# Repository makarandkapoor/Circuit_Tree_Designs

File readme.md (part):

## Synopsis

The folder contains embedded hardware designs mined/created by circuit tree hardware compiler. The designs are auto generated by scripts which generate each of the 900+ processors/microcontrollers parts with the various embedded component library list of circuit tree. Script help in generation of various design files and autogenerate componnent placements for the various dxf files present on circuit tree server. For additional details about the hardware compiler visit [Circuit Tree](https://circuit-tree.com). 

## Folder contents

Each folder contains design files generated on the circuit tree application server. It contains eagle, altium and orcad schematic files , bill of material, board layout snapshots from various dxf file to display auto generated component placement. 

Additional folder Development boards contains projects which have been fabricated and assembled. [Small Drone board](https://github.com/makarandkapoor/Circuit_Tree_Designs/tree/master/Development_boards/Small_drone_board) is a example board created with circuit tree hardware compiler. 

## Motivation

The purpose of generating design is to allow individuals to use vast generated design content without restriction and provide any feedback/improvement areas. 

## Fun Fact

Fun Fact: Each Design took 4-6 minutes to generate through scripts. We are talking about design generation, export of various EDA cad files, random board component placements of 6 boards for 900 + controllers that totals 3600 minutes(60 hrs)(Two and half day). 
It's time to look for a entry in some record book :) 

## Featured Hardware designs of the controllers
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
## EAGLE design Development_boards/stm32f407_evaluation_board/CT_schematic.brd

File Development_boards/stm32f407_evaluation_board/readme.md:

Contains the reference design files from the blog post

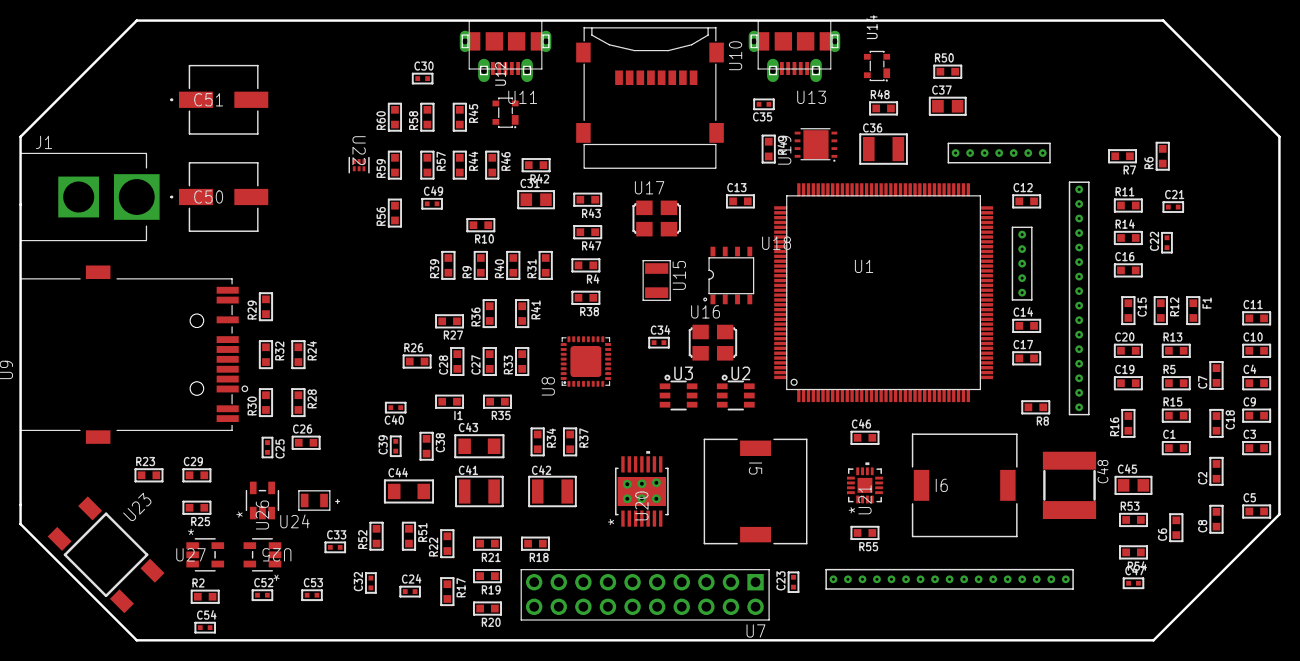
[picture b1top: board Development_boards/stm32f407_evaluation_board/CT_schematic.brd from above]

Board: 2 copper layers, 130.0 x 64.0 mm, 145 parts (0 on the bottom side), 118 nets, no tracks yet.

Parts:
C1, C20, C26, C27, C29, C38, C46: 1e-06; C0603
C2, C3, C4, C5, C6, C7, C8, C9, C10, C11, C12, C13, C17, C18: 1e-07; C0603
C14: 4.7e-06; C0603
C15, C16: 2.2e-06; C0603
C19: 1e-08; C0603
C21, C22: 1e-11; C0402
C23, C24, C30, C40, C47, C49: 1e-07; C0402
C25: 2.2e-08; C0402
C28: 4.7e-10; C0603
C31, C37, C45: 1e-05; C0805
C32, C33, C34, C35, C52, C53, C54: 1e-08; C0402
C36: 1e-05; C1210
C39: 3.3e-09; C0402
C41, C42: 2.2e-05; C1210
C43, C44: 1e-05; C1206
C48: 6.8e-05; 2220
C50, C51: 0.0001; EXV-9H
F1: 240.0; L0603
I1: 97.0; R0603
I5: 5.2e-06; DR1040
I6: 7e-06; DR1040
J1: PJ-037B; PJ-037B_PACKAGE
R2, R50: 1000.0; R0603
R4, R5: 4700.0; R0603
R6, R7, R8, R9, R10: 2200.0; R0603
R11, R12: 47000.0; R0603
R13, R14, R15, R16, R17, R18, R19, R20, R21, R22, R31, R33, R34, R35, R36, R37, R38, R39, R40, R41, R56, R57: 10000.0; R0603
R23, R24: 0.1; R0603
R25, R26, R49: 200.0; R0603
R27: 12100.0; R0603
R28, R29, R30, R32: 49.9; R0603
R42, R43, R44, R45, R46, R47, R48: 100000.0; R0603
R51: 71007.101651032; R0603
R52: 22000.0; R0603
R53: 20000.0; R0603
R54: 150000.0; R0603
R55: 300000.0; R0603
R58: 9100.0; R0603
R59: 680000.0; R0603
R60: 120000.0; R0603
U1: STM32F407ZET6; LQFP144
U2, U3: MAX4995AAUT+T; SOT-23-6
U4: dummy_connector_j2; DUMMY_PACKAGE_286
U5: dummy_connector_j4; DUMMY_PACKAGE_290
U6: dummy_connector_j5; DUMMY_PACKAGE_292
U7: TST-110-05-T-D-RA
U8: LAN8710AI-EZK; QFN-32
U9: 7498011122R
U10: 0472192001; MOLEX_47219-2001
U11, U13: 47590-0001; MICRO_USB_AB
U12, U14: prtr5v0u2ax; SOT143B
U15: ABS07-32.768KHZ-7-T
U16: ASFL1-25MHZ-NCS; ASFL1
U17: ASFL1-50MHZ-NCS; ASFL1
U18: idt74fct38072; IDT74FCT38072
U19: LP3878SDX-ADJ/NOPB; WSON-8
U20: tps54325PWP; HTSSOP14
U21: LTC3601EUD#PBF; QFN-16_EP
U22: TPS3895ADRYR; SON-6
U23: 4-1437565-2; SW_4-1437565-2
U24: Q65110A2395; LGM67K-G1J2-24-Z
U25, U26, U27: nc7sz125m5x; NC7SZ125M5X
U28: Dummy; DUMMY_PACKAGE_307

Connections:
CLK_CRYSTAL_U1_8: C21.1, U1.8, U15.1
CLK_CRYSTAL_U1_9: C22.1, U1.9, U15.2
CLK_U1_23: U1.23, U16.3
CLK_U1_35: U1.35, U18.7
CLK_U8_5: U8.5, U18.6
CLK_U18_3: U17.3, U18.3
GND: C1.2, C2.2, C3.2, C4.2, C5.2, C6.2, C7.2, C8.2, C9.2, C10.2, C11.2, C12.2, C13.2, C14.2, C15.2, C16.2, C17.2, C18.2, C19.2, C20.2, C21.2, C22.2, C23.2, C24.2, C25.2, C26.2, C27.2, C28.2, C29.2, C30.2, C31.2, C32.2, C33.2, C34.2, C35.2, C36.2, C37.2, C38.2, C39.2, C41.2, C42.2, C43.2, C44.2, C45.2, C46.2, C48.1, C49.2, C50.2, C51.2, C52.2, C53.2, C54.2, J1.2, R2.2, R11.2, R12.2, R14.2, R16.2, R22.2, R23.2, R24.2, R25.2, R27.2, R33.2, R41.2, R50.2, R52.2, R53.2, R55.2, R58.2, R60.2, U1.16, U1.31, U1.38, U1.51, U1.61, U1.83, U1.94, U1.107, U1.120, U1.130, U2.2, U3.2, U4.1, U4.6, U4.11, U5.1, U6.1, U6.6, U7.4, U7.6, U7.8, U7.10, U7.12, U7.14, U7.16, U7.18, U7.20, U8.24, U8.25, U8.EXP, U10.6, U10.G1, U10.G2, U10.G3, U10.G4, U11.5, U12.1, U13.5, U14.1, U16.2, U17.2, U18.4, U18.5, U18.8, U19.3, U19.PAD, U20.5, U21.1, U21.9, U21.17, U22.2, U24.C, U25.2, U25.3, U26.1, U26.3, U27.1, U27.3, U28.1, U28.6, U28.11, U28.16
NET_U1_10: R7.1, U1.10, U4.8
NET_U1_11: R6.1, U1.11, U4.7
NET_U1_12: R8.1, U1.12, U4.9
NET_U1_25: R5.1, U1.25, U27.4
NET_U1_27: R9.1, U1.27, U8.17
NET_U1_33: C17.1, C18.1, C19.1, C20.1, F1.1, U1.32, U1.33
NET_U1_36: R10.1, U1.36, U8.16
NET_U1_71: C15.1, U1.71
NET_U1_106: C16.1, U1.106
NET_U1_138: R14.1, U1.138
NET_U1_143: R13.1, U1.143
NET_U2_3: R11.1, U2.3
NET_U3_3: R12.1, U3.3
NET_U7_19: R22.1, U7.19
NET_U8_1: C26.1, I1.1, R28.2, R29.2, R30.2, R32.2, R35.2, U8.1, U8.27, U9.2, U9.9
NET_U8_3: R35.1, U8.3
NET_U8_7: R40.1, U8.7
NET_U8_8: R41.1, U8.8
NET_U8_9: R33.1, R34.1, U8.9
NET_U8_13: R39.1, U8.13
NET_U8_18: R31.1, U8.18
NET_U8_19: R4.1, U8.19, U26.4
NET_U8_32: R27.1, U8.32
NET_U9_1: R28.1, U8.29, U9.1
NET_U9_3: R26.2, R29.1, U8.28, U9.3
NET_U9_4: R30.1, U8.31, U9.4
NET_U9_5: C25.1, U9.2, U9.5
NET_U9_6: R32.1, U8.30, U9.6
NET_U9_8: R24.1, U9.8
NET_U9_10: R26.1, U9.10
NET_U9_11: U8.2, U9.11
NET_U9_12: R25.1, U9.12
NET_U9_13: R23.1, U9.13, U9.14
NET_U11_6: U11.6, U11.7, U11.8, U11.9
NET_U13_6: U13.6, U13.7, U13.8, U13.9
NET_U19_1: C35.1, U19.1
NET_U19_6: R49.2, R50.1, U19.6
NET_U19_8: R48.1, U19.8
NET_U20_2: R51.2, R52.1, U20.2
NET_U20_3: C38.1, U20.3
NET_U20_4: C39.1, U20.4
NET_U20_8: U20.8, U20.9
NET_U20_10: C40.1, I5.1, U20.10, U20.11
NET_U20_12: C40.2, U20.12
NET_U21_3: C47.2, I6.1, U21.3, U21.4
NET_U21_6: C47.1, U21.6
NET_U21_7: C46.1, U21.7, U21.12
NET_U21_10: R55.1, U21.10
NET_U21_11: R53.1, R54.1, U21.11
NET_U21_ATNET_3: C48.2, I6.2, R54.2
NET_U22_1: R57.1, R58.1, U22.1
NET_U22_3: R59.2, R60.1, U22.3
NET_U22_4: R56.1, U22.4, U25.4, U26.2, U27.2
NET_U23_1: R2.1, U23.1, U23.2
PROC_ETH_CRS_DV: R38.1, U1.43, U8.15
PROC_ETH_RXD0: R36.1, U1.44, U8.11
PROC_ETH_RXD1: R37.1, U1.45, U8.10
PROC_ETH_TXD0: U1.128, U8.22
PROC_ETH_TXD1: U1.129, U8.23
PROC_ETH_TX_EN: U1.70, U8.21
PROC_GPIO_TO_U1_USB_FAULT: R15.1, U1.2, U2.6
PROC_GPIO_TO_U1_USB_FAULT2: U1.4, U3.6
PROC_GPIO_TO_U1_VBUS_EN: R16.1, U1.1, U2.4
PROC_GPIO_TO_U1_VBUS_EN2: U1.3, U3.4
PROC_PC13_ANTI_TAMP: U1.7, U28.3
PROC_PE6: U1.5, U28.2
PROC_PF3: U1.13, U28.4
PROC_PF4: U1.14, U28.5
PROC_PF5: U1.15, U28.7
PROC_PF6: U1.18, U28.8
PROC_PF7: U1.19, U28.9
PROC_PF8: U1.20, U28.10
PROC_PF9: U1.21, U28.12
PROC_PF10: U1.22, U28.13
PROC_PH1_OSC_OUT: U1.24, U28.14
PROC_SDIO_CK: R43.1, U1.113, U10.5
PROC_SDIO_CMD: R42.1, U1.116, U10.3
PROC_SDIO_D0: R44.1, U1.98, U10.7
PROC_SDIO_D1: R45.1, U1.99, U10.8
PROC_SDIO_D2: R46.1, U1.111, U10.1
PROC_SDIO_D3: R47.1, U1.112, U10.2
PROC_SPI1_MISO: U1.42, U4.3
PROC_SPI1_MOSI: U1.135, U4.2
PROC_SPI1_NSS: U1.40, U4.5
PROC_SPI1_SCK: U1.41, U4.4
PROC_SPI2_MISO: U1.28, U5.2
PROC_SPI2_MOSI: U1.29, U5.4
PROC_SPI2_NSS: U1.140, U5.5
PROC_SPI2_SCK: U1.69, U5.3
PROC_SYS_JTCK_SWCLK: R20.1, U1.109, U7.9
PROC_SYS_JTDI: R18.1, U1.110, U7.5
PROC_SYS_JTDO_SWO: U1.133, U7.13
PROC_SYS_JTMS_SWDIO: R19.1, U1.105, U7.7
PROC_SYS_JTRST: R17.1, U1.134, U7.3
PROC_USART2_RX: U1.37, U4.10
PROC_USART2_TX: U1.119, U4.12
PROC_USART3_RX: U1.78, U6.3
PROC_USART3_TX: U1.77, U6.2
PROC_USB_OTG_FS_DM: U1.103, U11.2, U12.3
PROC_USB_OTG_FS_DP: U1.104, U11.3, U12.2
PROC_USB_OTG_FS_ID: U1.102, U11.4
PROC_USB_OTG_FS_VBUS: U1.101, U2.1, U11.1, U12.4
PROC_USB_OTG_HS_DM: U1.75, U13.2, U14.3
PROC_USB_OTG_HS_DP: U1.76, U13.3, U14.2
PROC_USB_OTG_HS_ID: U1.73, U13.4
PROC_USB_OTG_HS_VBUS: U1.74, U3.1, U13.1, U14.4
RST_OUT_U7_SRESET_B: R21.1, U7.15, U25.1
VCC_S1_14: C36.1, C43.1, C44.1, C45.1, C50.1, C51.1, J1.1, R48.2, U19.4, U20.7, U20.13, U20.14, U21.15, U21.16
VCC_TIER1_1V2: C27.1, C28.1, C37.1, R49.1, U8.6, U19.5
VCC_TIER1_3V3: C1.1, C2.1, C3.1, C4.1, C5.1, C6.1, C7.1, C8.1, C9.1, C10.1, C11.1, C12.1, C13.1, C14.1, C23.1, C24.1, C29.1, C30.1, C31.1, C32.1, C33.1, C34.1, C41.1, C42.1, C49.1, C52.1, C53.1, C54.1, F1.2, I1.2, I5.2, R4.2, R5.2, R6.2, R7.2, R8.2, R9.2, R10.2, R13.2, R15.2, R17.2, R18.2, R19.2, R20.2, R21.2, R31.2, R34.2, R36.2, R37.2, R38.2, R39.2, R40.2, R42.2, R43.2, R44.2, R45.2, R46.2, R47.2, R51.1, R56.2, R57.2, R59.1, U1.6, U1.17, U1.30, U1.39, U1.52, U1.62, U1.72, U1.84, U1.95, U1.108, U1.121, U1.131, U1.144, U7.1, U7.2, U8.12, U10.4, U16.4, U17.4, U18.1, U18.2, U20.1, U22.6, U25.5, U26.5, U27.5
VCC_TIER1_5V0: C48.2, I6.2, R54.2, U2.5, U3.5, U21.8

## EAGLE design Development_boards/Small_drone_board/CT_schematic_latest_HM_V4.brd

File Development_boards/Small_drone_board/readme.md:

## Introduction
Drone hardware design created with circuit tree web application. Details of the project are to be found on the page [Drone Design Blog](http://circuit-tree.com/small-drone-design/);
The Project design files are in eagle so you will need eagle viewer for the project. 

## Folder contents
- Circuit Tree Generated schematic [CT_schematic.sch](https://github.com/makarandkapoor/Circuit_Tree_Designs/blob/master/Development_boards/Small_drone_board/CT_schematic.sch) and board [CT_schematic.brd](https://github.com/makarandkapoor/Circuit_Tree_Designs/blob/master/Development_boards/Small_drone_board/CT_schematic.brd) files 
- Released Design files with manual edits [CT_schematic_latest_HM_V4.sch](https://github.com/makarandkapoor/Circuit_Tree_Designs/blob/master/Development_boards/Small_drone_board/CT_schematic_latest_HM_V4.sch) and [CT_schematic_latest_HM_V4.brd](https://github.com/makarandkapoor/Circuit_Tree_Designs/blob/master/Development_boards/Small_drone_board/CT_schematic_latest_HM_V4.brd)
- [Project Block diagram](https://github.com/makarandkapoor/Circuit_Tree_Designs/blob/master/Development_boards/Small_drone_board/block_diagram.png)

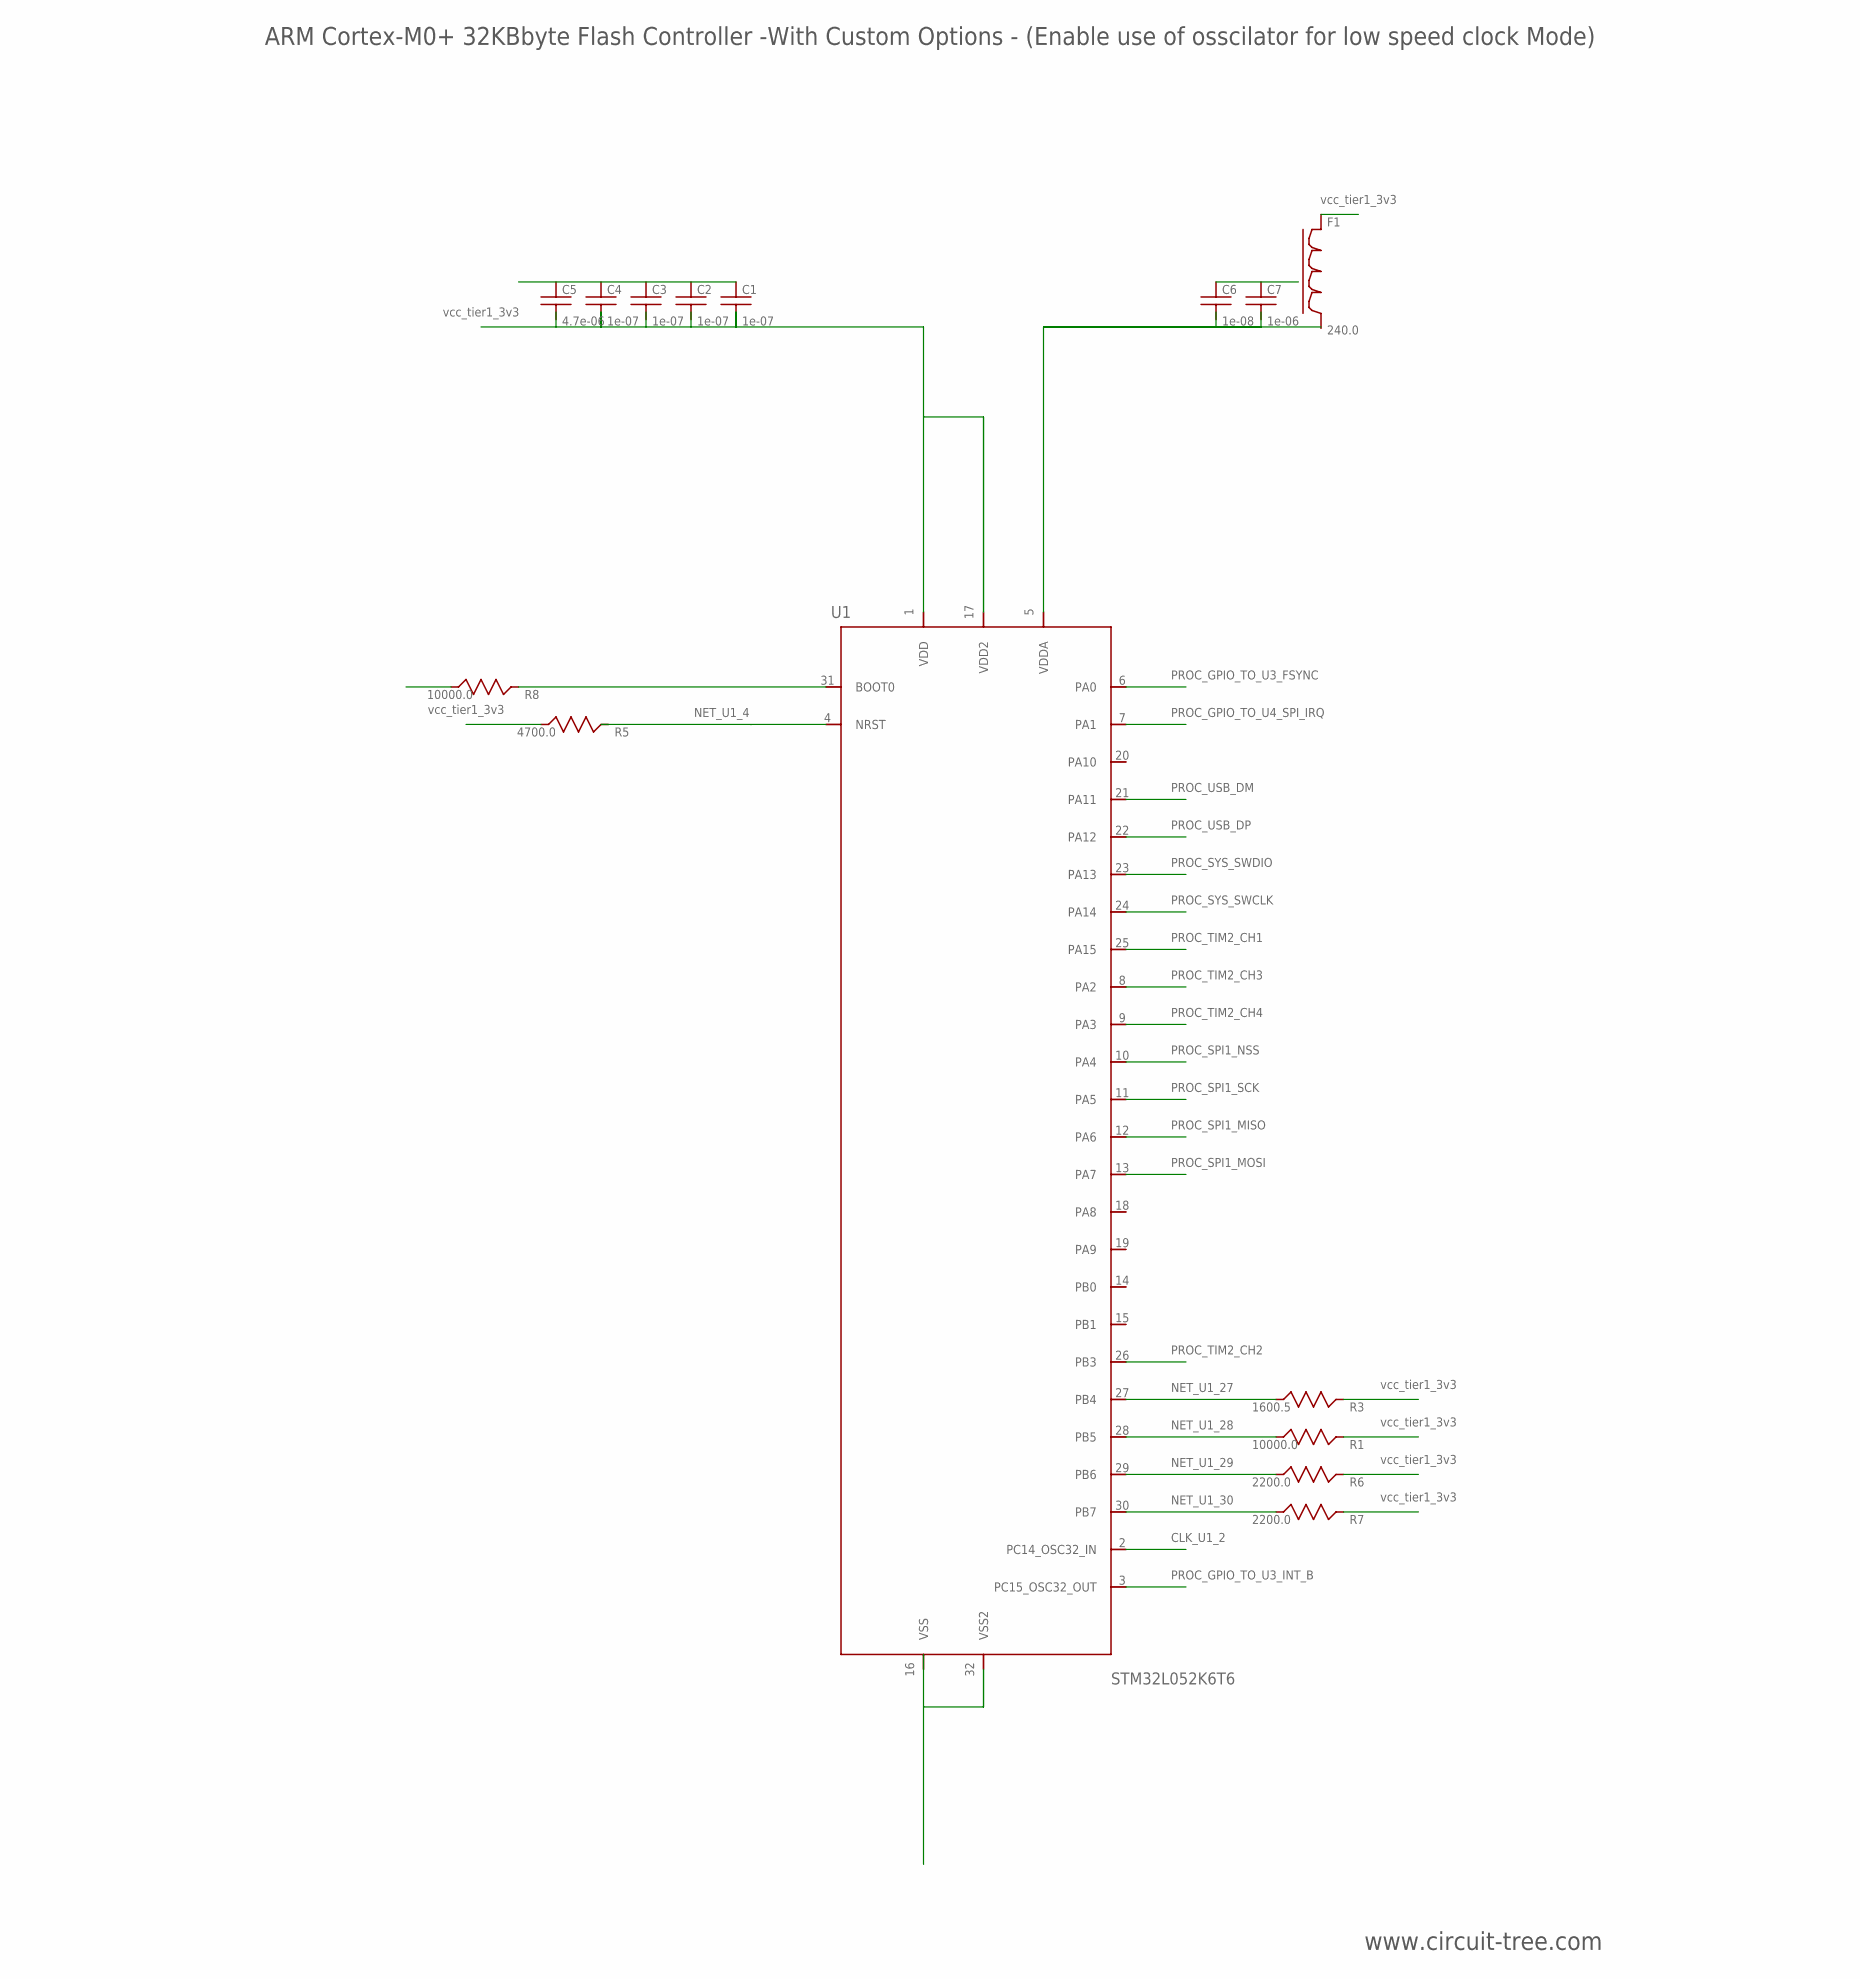
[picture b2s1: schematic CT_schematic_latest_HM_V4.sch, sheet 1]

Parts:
C1, C2, C3, C4: 1e-07; C0603
C5: 4.7e-06; C0603
C6: 1e-08; C0603
C7: 1e-06; C0603
F1: 240.0; L0603
R1, R8: 10000.0; R0603
R3: 1600.5; R0603
R5: 4700.0; R0603
R6, R7: 2200.0; R0603
U1: STM32L052K6T6; LQFP32

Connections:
CLK_U1_2: U1.2 (PC14_OSC32_IN); also elsewhere on the board
GND: C1.2, C2.2, C3.2, C4.2, C5.2, C6.2, C7.2, R8.2, U1.16 (VSS), U1.32 (VSS2); also elsewhere on the board
NET_U1_4: R5.1, U1.4 (NRST); also elsewhere on the board
NET_U1_5: C6.1, C7.1, F1.1, U1.5 (VDDA)
NET_U1_27: R3.1, U1.27 (PB4); also elsewhere on the board
NET_U1_28: R1.1, U1.28 (PB5); also elsewhere on the board
NET_U1_29: R6.1, U1.29 (PB6); also elsewhere on the board
NET_U1_30: R7.1, U1.30 (PB7); also elsewhere on the board
NET_U1_31: R8.1, U1.31 (BOOT0)
PROC_GPIO_TO_U3_FSYNC: U1.6 (PA0); also elsewhere on the board
PROC_GPIO_TO_U3_INT_B: U1.3 (PC15_OSC32_OUT); also elsewhere on the board
PROC_GPIO_TO_U4_SPI_IRQ: U1.7 (PA1); also elsewhere on the board
PROC_SPI1_MISO: U1.12 (PA6); also elsewhere on the board
PROC_SPI1_MOSI: U1.13 (PA7); also elsewhere on the board
PROC_SPI1_NSS: U1.10 (PA4); also elsewhere on the board
PROC_SPI1_SCK: U1.11 (PA5); also elsewhere on the board
PROC_SYS_SWCLK: U1.24 (PA14); also elsewhere on the board
PROC_SYS_SWDIO: U1.23 (PA13); also elsewhere on the board
PROC_TIM2_CH1: U1.25 (PA15); also elsewhere on the board
PROC_TIM2_CH2: U1.26 (PB3); also elsewhere on the board
PROC_TIM2_CH3: U1.8 (PA2); also elsewhere on the board
PROC_TIM2_CH4: U1.9 (PA3); also elsewhere on the board
PROC_USB_DM: U1.21 (PA11); also elsewhere on the board
PROC_USB_DP: U1.22 (PA12); also elsewhere on the board
VCC_TIER1_3V3: C1.1, C2.1, C3.1, C4.1, C5.1, F1.2, R1.2, R3.2, R5.2, R6.2, R7.2, U1.1 (VDD), U1.17 (VDD2); also elsewhere on the board

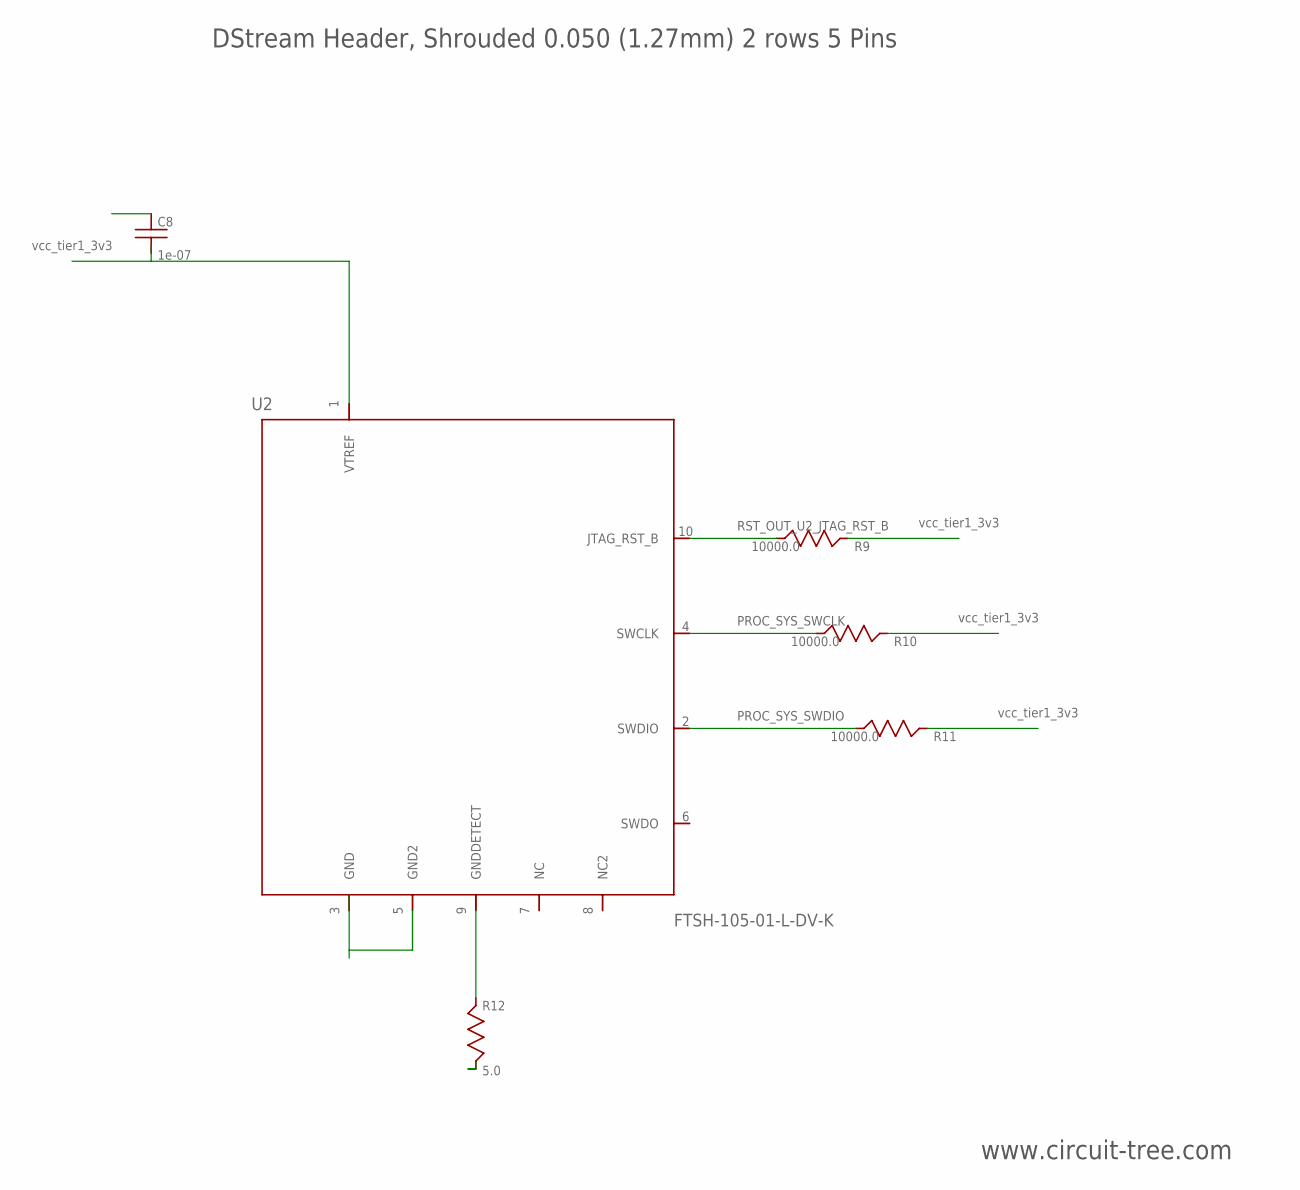
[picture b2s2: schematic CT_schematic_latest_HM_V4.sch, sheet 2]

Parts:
C8: 1e-07; C0402
R9, R10, R11: 10000.0; R0603
R12: 5.0; R0603
U2: FTSH-105-01-L-DV-K; SAMTEC_FTSH-105-01-L-DV-K

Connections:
GND: C8.2, R12.2, U2.3 (GND), U2.5 (GND2); also elsewhere on the board
NET_U2_9: R12.1, U2.9 (GNDDETECT)
PROC_SYS_SWCLK: R10.1, U2.4 (SWCLK); also elsewhere on the board
PROC_SYS_SWDIO: R11.1, U2.2 (SWDIO); also elsewhere on the board
RST_OUT_U2_JTAG_RST_B: R9.1, U2.10 (JTAG_RST_B); also elsewhere on the board
VCC_TIER1_3V3: C8.1, R9.2, R10.2, R11.2, U2.1 (VTREF); also elsewhere on the board

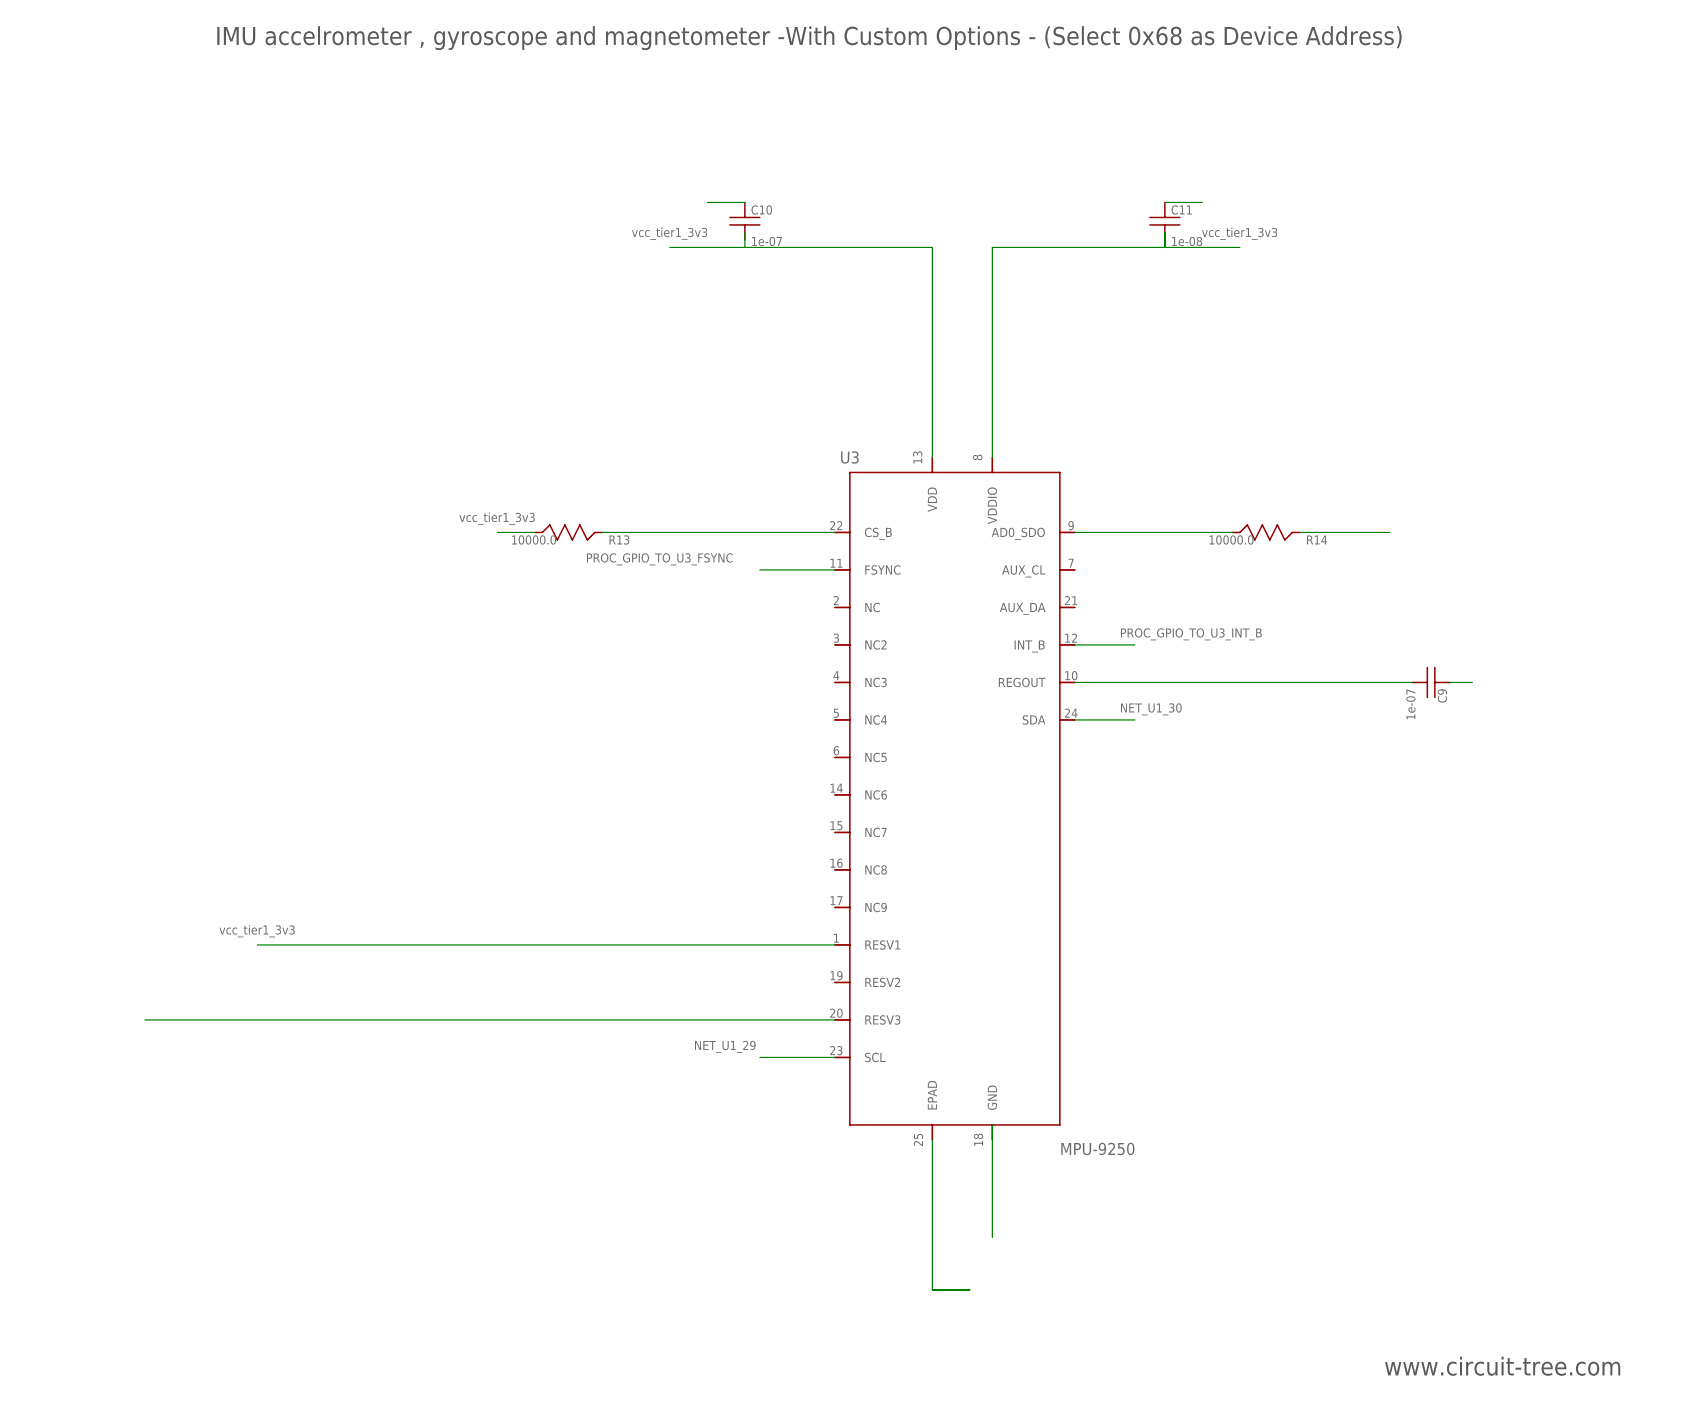
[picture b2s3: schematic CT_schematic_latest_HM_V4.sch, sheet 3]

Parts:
C9, C10: 1e-07; C0402
C11: 1e-08; C0402
R13, R14: 10000.0; R0603
U3: MPU-9250; QFN24_2

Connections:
GND: C9.2, C10.2, C11.2, R14.2, U3.18 (GND), U3.20 (RESV3), U3.25 (EPAD); also elsewhere on the board
NET_U1_29: U3.23 (SCL); also elsewhere on the board
NET_U1_30: U3.24 (SDA); also elsewhere on the board
NET_U3_9: R14.1, U3.9 (AD0_SDO)
NET_U3_10: C9.1, U3.10 (REGOUT)
NET_U3_22: R13.1, U3.22 (CS_B)
PROC_GPIO_TO_U3_FSYNC: U3.11 (FSYNC); also elsewhere on the board
PROC_GPIO_TO_U3_INT_B: U3.12 (INT_B); also elsewhere on the board
VCC_TIER1_3V3: C10.1, C11.1, R13.2, U3.1 (RESV1), U3.8 (VDDIO), U3.13 (VDD); also elsewhere on the board

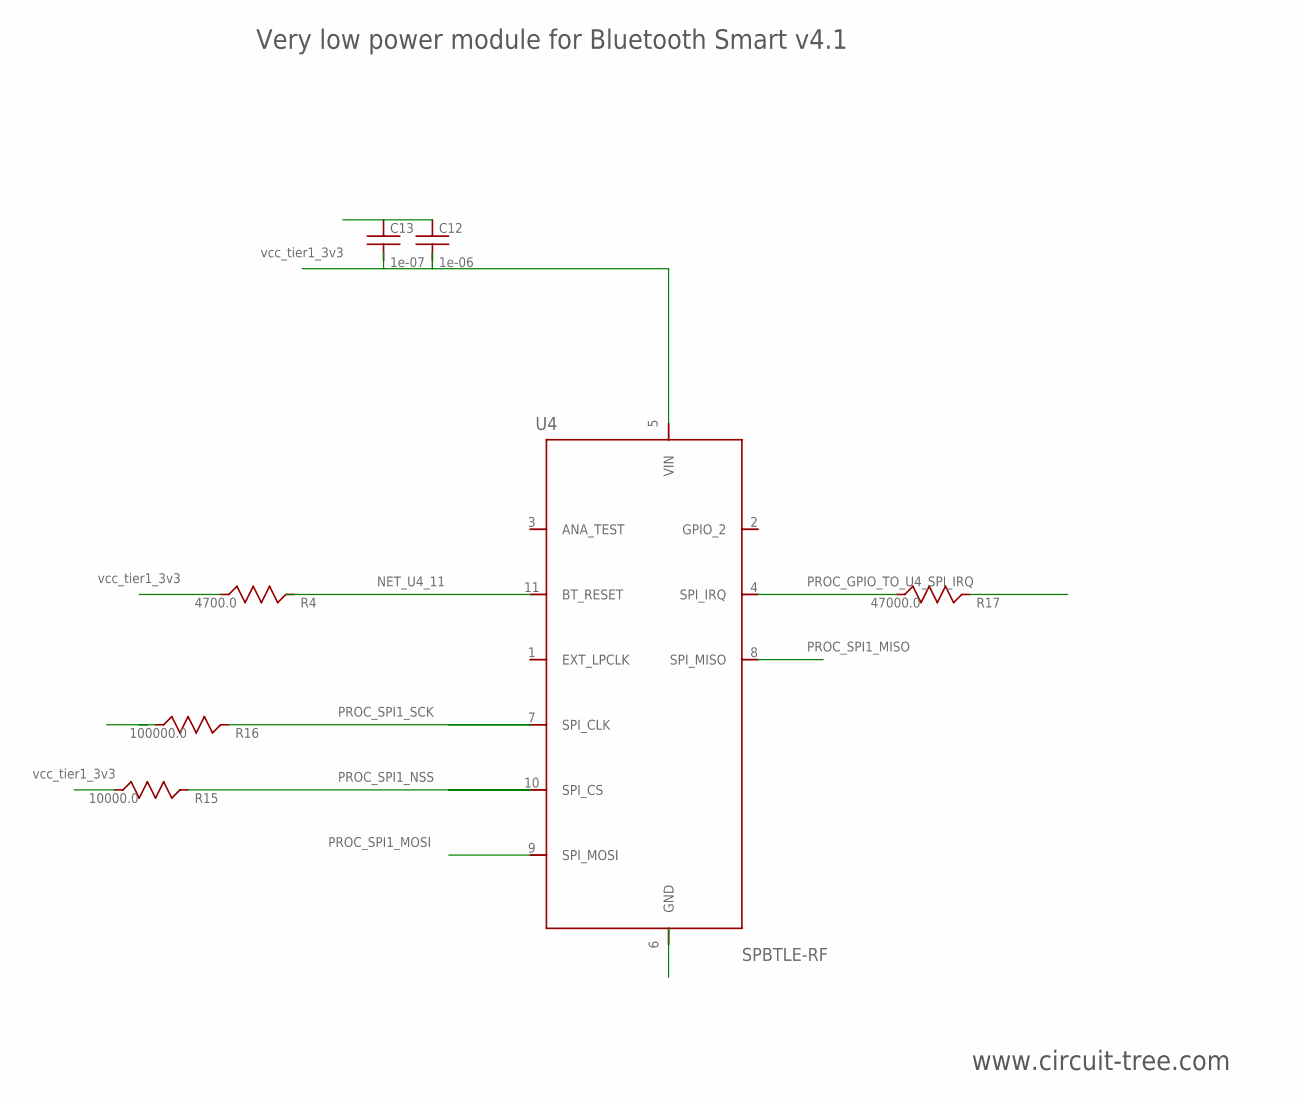
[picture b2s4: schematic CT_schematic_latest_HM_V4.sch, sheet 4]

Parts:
C12: 1e-06; C0603
C13: 1e-07; C0402
R4: 4700.0; R0603
R15: 10000.0; R0603
R16: 100000.0; R0603
R17: 47000.0; R0603
U4: SPBTLE-RF; XCVR_SPBTLE-RF

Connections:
GND: C12.2, C13.2, R16.2, R17.2, U4.6 (GND); also elsewhere on the board
NET_U4_11: R4.1, U4.11 (BT_RESET); also elsewhere on the board
PROC_GPIO_TO_U4_SPI_IRQ: R17.1, U4.4 (SPI_IRQ); also elsewhere on the board
PROC_SPI1_MISO: U4.8 (SPI_MISO); also elsewhere on the board
PROC_SPI1_MOSI: U4.9 (SPI_MOSI); also elsewhere on the board
PROC_SPI1_NSS: R15.1, U4.10 (SPI_CS); also elsewhere on the board
PROC_SPI1_SCK: R16.1, U4.7 (SPI_CLK); also elsewhere on the board
VCC_TIER1_3V3: C12.1, C13.1, R4.2, R15.2, U4.5 (VIN); also elsewhere on the board

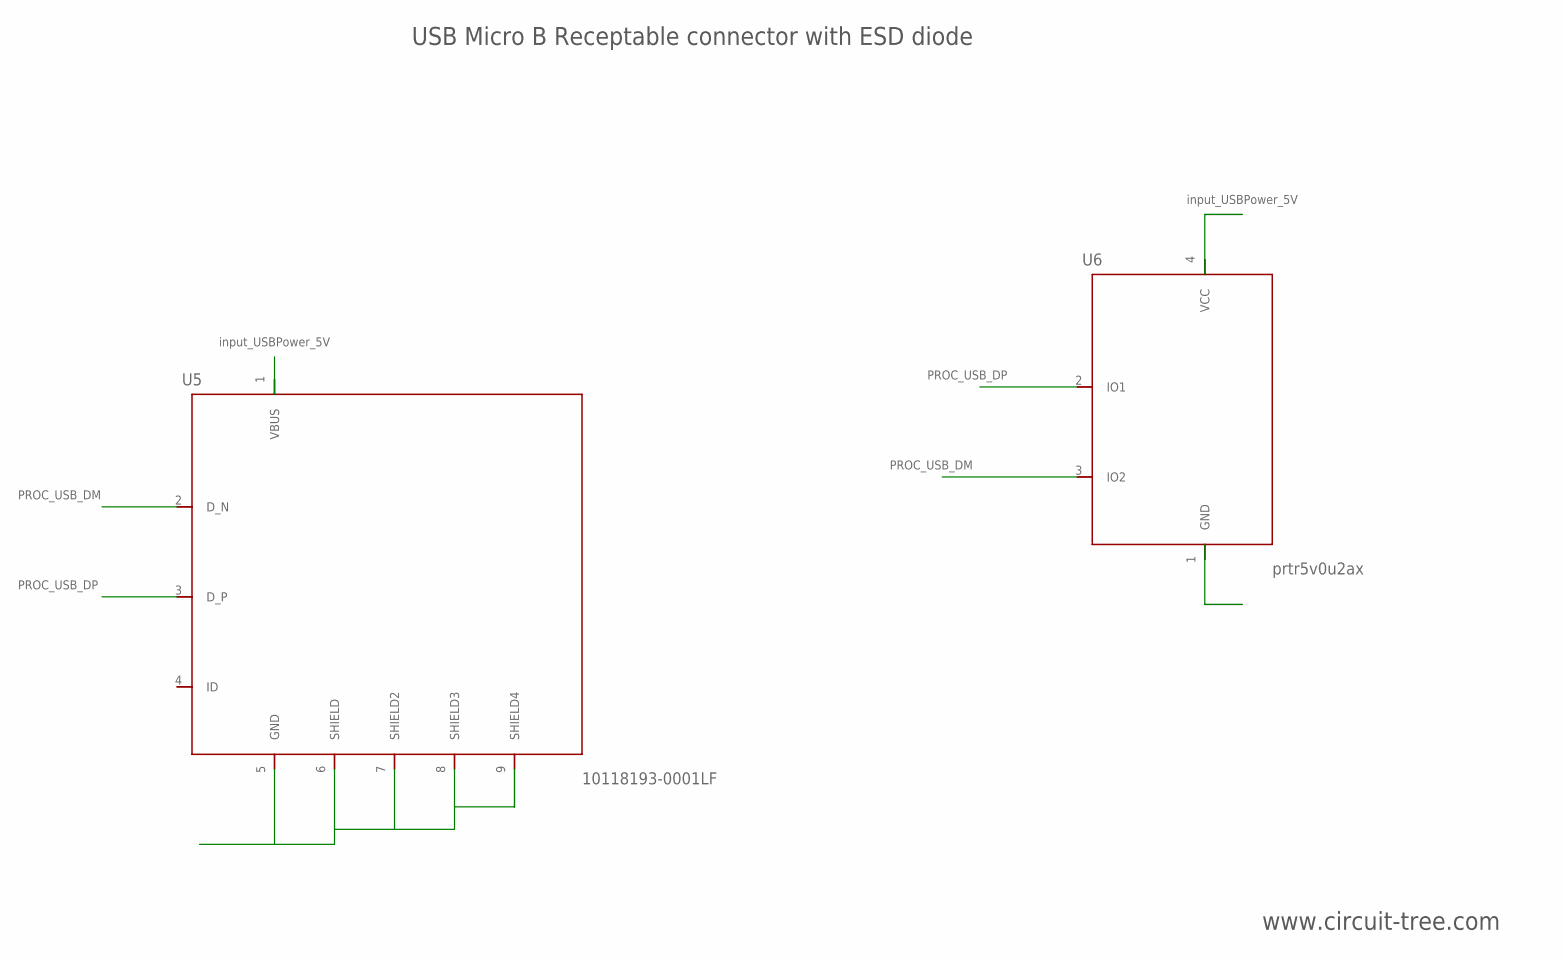
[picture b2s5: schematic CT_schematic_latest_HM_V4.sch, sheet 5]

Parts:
U5: 10118193-0001LF; FCI_10118193-0001LF
U6: prtr5v0u2ax; SOT143B

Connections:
GND: U5.5 (GND), U5.6 (SHIELD), U5.7 (SHIELD2), U5.8 (SHIELD3), U5.9 (SHIELD4), U6.1 (GND); also elsewhere on the board
INPUT_USBPOWER_5V: U5.1 (VBUS), U6.4 (VCC); also elsewhere on the board
PROC_USB_DM: U5.2 (D_N), U6.3 (IO2); also elsewhere on the board
PROC_USB_DP: U5.3 (D_P), U6.2 (IO1); also elsewhere on the board

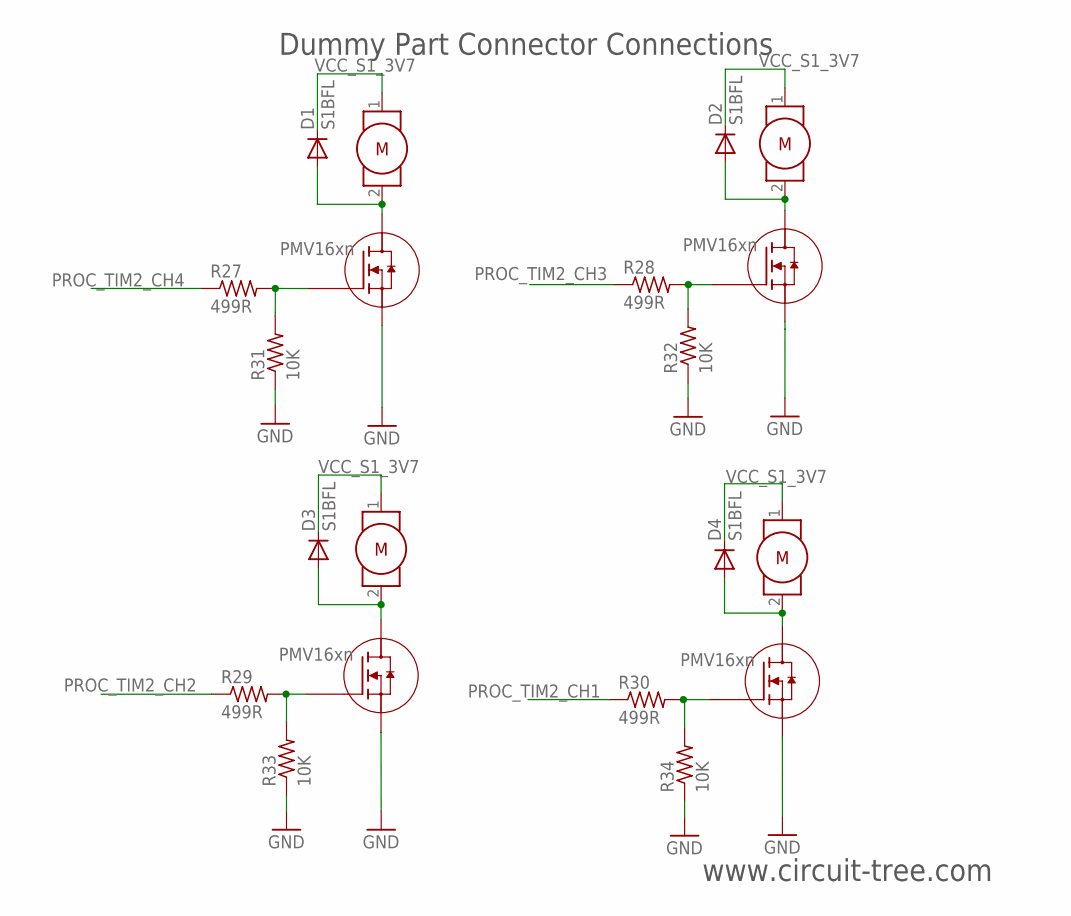
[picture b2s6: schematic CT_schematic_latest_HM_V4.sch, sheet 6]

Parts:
D1, D2, D3, D4: S1BFL; SOD123
Q1, Q2, Q3, Q4: PMV16XN; SOT23
R27, R28, R29, R30: 499R; R0603
R31, R32, R33, R34: 10K; R0603
U$1, U$2, U$3, U$4: MOTOR; M-2-SMD

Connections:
GND: Q1.2 (S), Q2.2 (S), Q3.2 (S), Q4.2 (S), R31.1, R32.1, R33.1, R34.1; also elsewhere on the board
unnamed: Q1.1 (G), R27.2, R31.2
unnamed: Q2.1 (G), R28.2, R32.2
unnamed: Q4.1 (G), R30.2, R34.2
unnamed: Q3.1 (G), R29.2, R33.2
unnamed: D1.A, Q1.3 (D), U$1.2
unnamed: D2.A, Q2.3 (D), U$2.2
unnamed: D3.A, Q3.3 (D), U$3.2
unnamed: D4.A, Q4.3 (D), U$4.2
PROC_TIM2_CH1: R30.1; also elsewhere on the board
PROC_TIM2_CH2: R29.1; also elsewhere on the board
PROC_TIM2_CH3: R28.1; also elsewhere on the board
PROC_TIM2_CH4: R27.1; also elsewhere on the board
VCC_S1_3V7: D1.C, D2.C, D3.C, D4.C, U$1.1, U$2.1, U$3.1, U$4.1; also elsewhere on the board

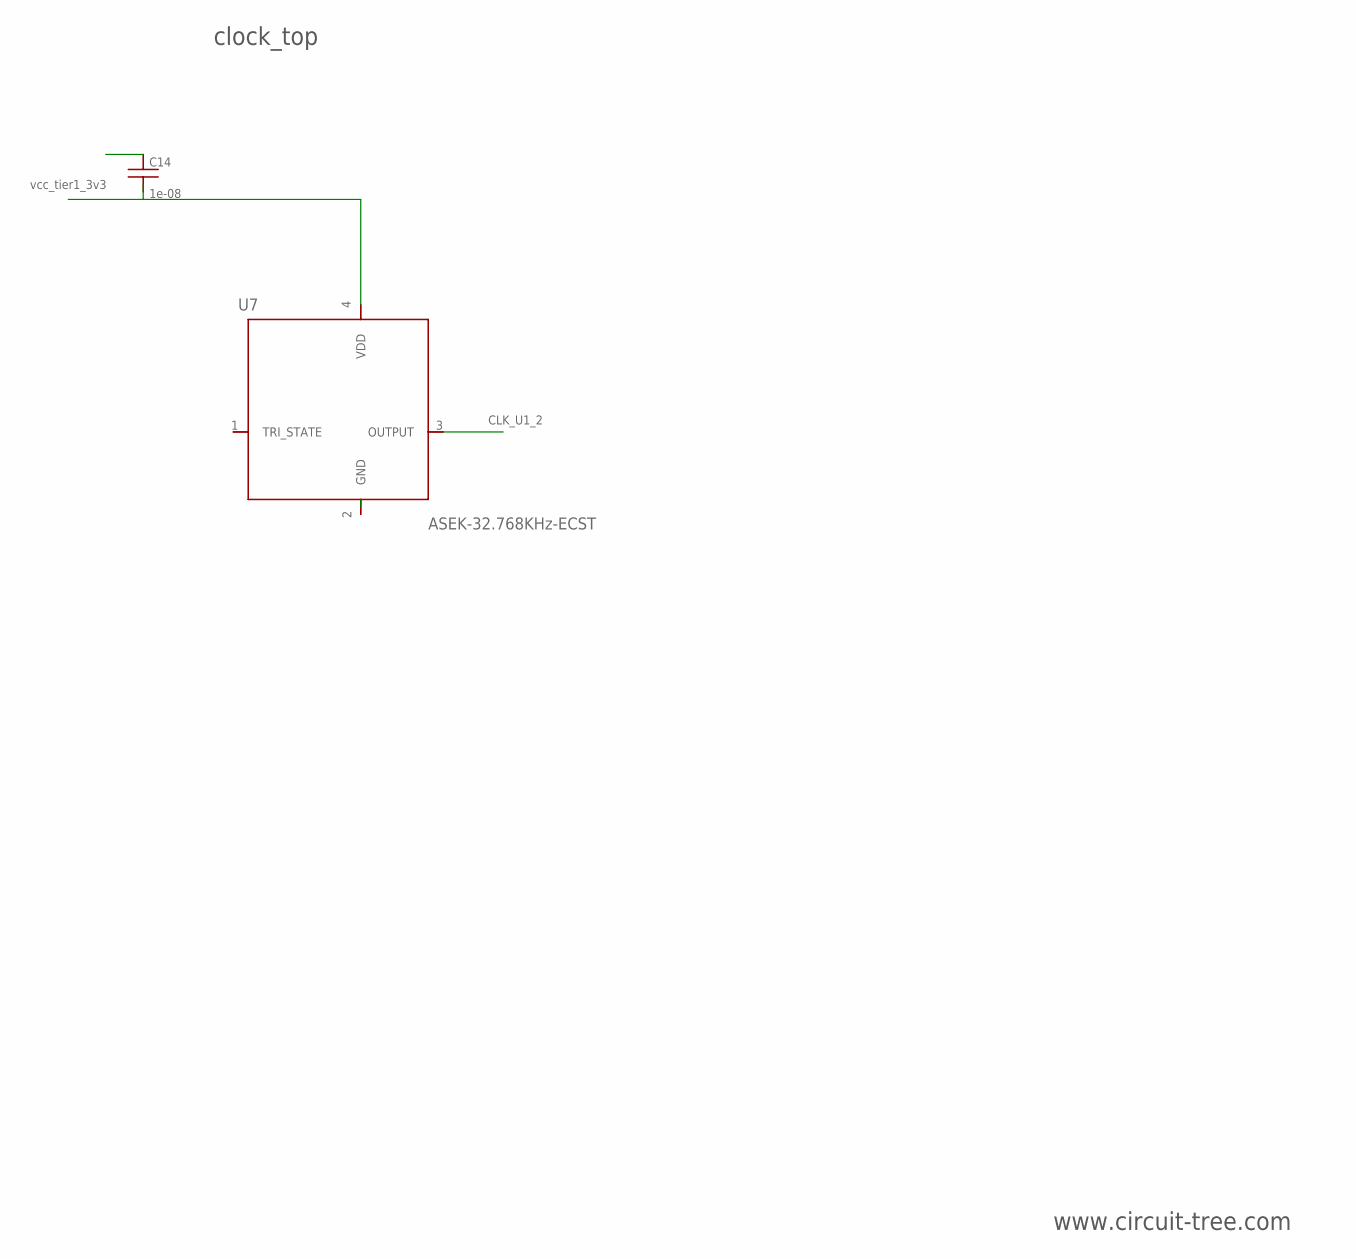
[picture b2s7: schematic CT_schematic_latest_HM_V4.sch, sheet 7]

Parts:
C14: 1e-08; C0402
U7: ASEK-32.768KHz-ECST; ASEK

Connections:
CLK_U1_2: U7.3 (OUTPUT); also elsewhere on the board
GND: C14.2, U7.2 (GND); also elsewhere on the board
VCC_TIER1_3V3: C14.1, U7.4 (VDD); also elsewhere on the board

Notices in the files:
parts and their libraries:
circuit_tree: (C) 2014 Tomasz Boleslaw CEDRO, cederom@tlen.pl, http://www.tomek.cedro.info.
